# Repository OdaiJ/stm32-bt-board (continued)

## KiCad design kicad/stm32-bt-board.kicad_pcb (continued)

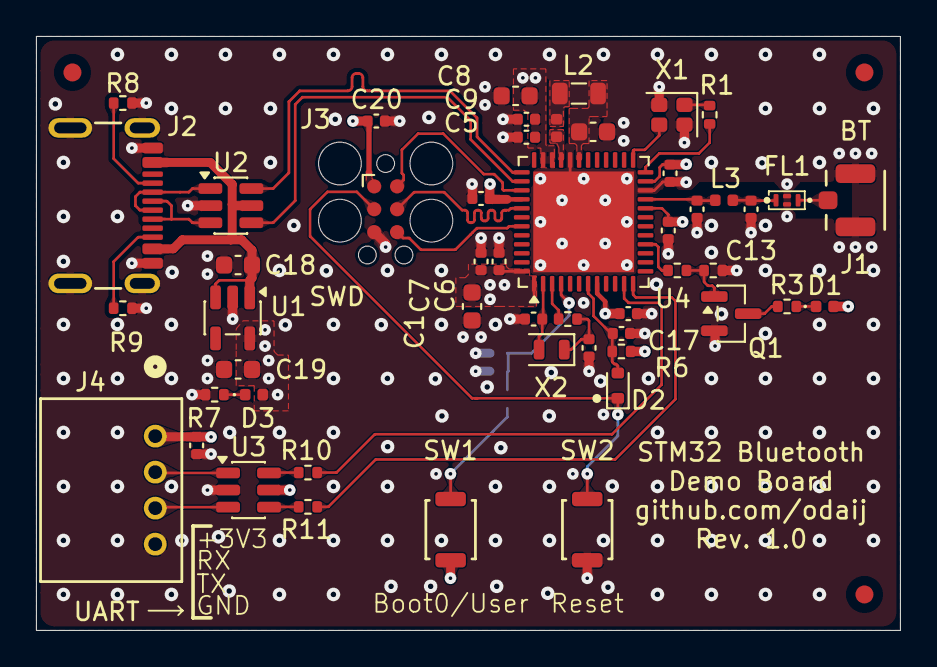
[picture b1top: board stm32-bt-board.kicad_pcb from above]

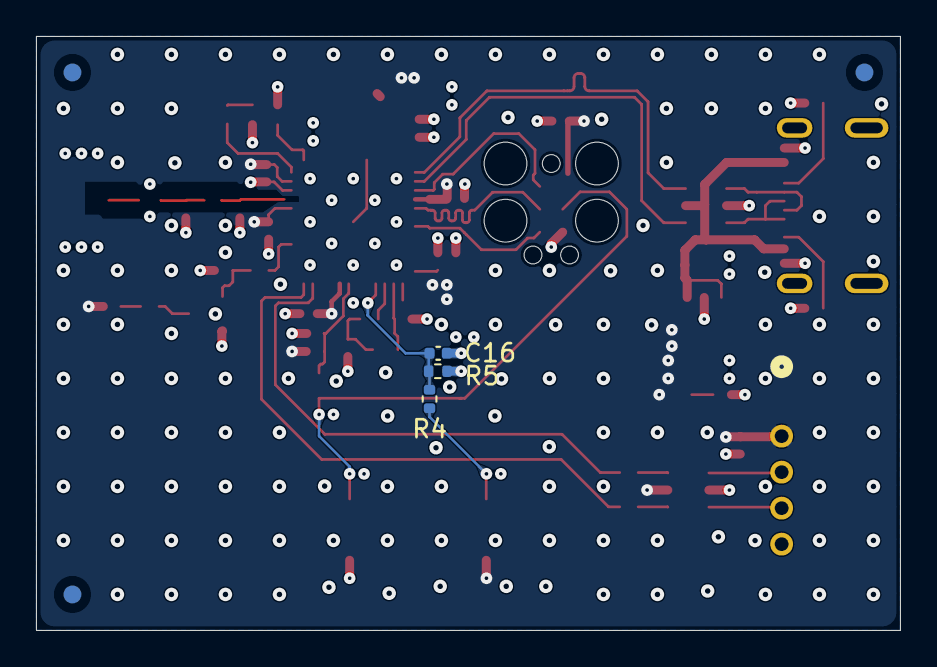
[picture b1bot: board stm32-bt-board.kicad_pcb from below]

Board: 4 copper layers, 48.0 x 33.0 mm, 60 parts (6 on the bottom side), 39 nets.

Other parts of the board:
FID1, FID2, FID3: Fiducial_1mm_Mask2mm
FID4, FID5, FID6: Fiducial; Fiducial_1mm_Mask2mm

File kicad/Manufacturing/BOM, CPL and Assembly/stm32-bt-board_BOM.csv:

"Reference","Qty","Value","DNP","Exclude from BOM","Exclude from Board","Footprint","Datasheet","Distributor","Distributor Link","Manufacturer","MPN","Description"
"C1,C8,C11,C18,C19","5","4u7","","","","Capacitor_SMD:C_0603_1608Metric","https://www.lcsc.com/datasheet/C307467.pdf?spm=wm.sxq.inf.gg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","LCSC","https://www.lcsc.com/product-detail/C307467.html?spm=wm.fly.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","Samsung Electro-Mechanics","CL10A475KL8NRNC","CAP CER 4.7uF 35V X5R 0603"
"C2,C3,C4,C5,C6,C7,C9,C10,C16,C17,C20,C21","12","100n","","","","Capacitor_SMD:C_0402_1005Metric","https://www.lcsc.com/datasheet/C60474.pdf?spm=wm.sxq.inf.ggs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","LCSC","https://www.lcsc.com/product-detail/C60474.html?s_z=s_p_CC04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","YAGEO","CC0402KRX7R7BB104","CAP CER 100nF 16V X7R 0402"
"C12","1","0p8","","","","Capacitor_SMD:C_0402_1005Metric","https://www.lcsc.com/datasheet/C76988.pdf?spm=wm.sxq.inf.ggs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","LCSC","https://www.lcsc.com/product-detail/C76988.html?s_z=s_p_GRM1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","muRata","GRM1555C1HR80BA01D","CAP CER 0.8pF 50V C0G 0402"
"C13","1","0p3","","","","Capacitor_SMD:C_0402_1005Metric","https://www.lcsc.com/datasheet/C92338.pdf?spm=wm.sxq.inf.ggs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","LCSC","https://www.lcsc.com/product-detail/C92338.html?s_z=s_p_GRM1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","muRata","GRM1555C1HR30WA01D","CAP CER 0.3pF 50V C0G 0402"
"C14,C15","2","10p","","","","Capacitor_SMD:C_0402_1005Metric","https://www.lcsc.com/datasheet/C161520.pdf","LCSC","https://www.lcsc.com/product-detail/C161520.html","muRata","GRM1555C1H100FA01D","CAP CER 10pF 50V C0G 0402"
"D1","1","VLMB1500-GS08","","","","LED_SMD:LED_0402_1005Metric","https://www.lcsc.com/datasheet/C511042.pdf?spm=wm.sxq.inf.gg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","LCSC","https://www.lcsc.com/product-detail/C511042.html?s_z=s_p_VLM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","VISHAY","VLMB1500-GS08","LED BLUE 0402 SMD"
"D2","1","BAT54K","","","","Diode_SMD:D_SOD-523","https://www.lcsc.com/datasheet/C283259.pdf?spm=wm.sxq.inf.gg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","LCSC","https://www.lcsc.com/product-detail/C283259.html?s_z=s_p_BAT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","ST","BAT54KFILM","DIODE SCHOTTKY 40V SOD-523"
"D3","1","VLMS1500-GS08","","","","LED_SMD:LED_0402_1005Metric","https://www.lcsc.com/datasheet/C511370.pdf?spm=wm.sxq.inf.gg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","LCSC","https://www.lcsc.com/product-detail/C511370.html?spm=wm.fly.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","VISHAY","VLMS1500-GS08","LED RED 0402 SMD"
"FL1","1","DLF162500LT-5028A1","","","","#stm32-bt-board-external-footprints:DLF162500LT-5028A1","https://product.tdk.com/en/system/files/dam/doc/product/rf/r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","LCSC","https://www.lcsc.com/product-detail/C531364.html?s_z=s_p_DLF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","TDK","DLF162500LT-5028A1","Multilayer Low Pass Filter For 2400-2500MHz"
"J1","1","1909763-1","","","","#stm32-bt-board-external-footprints:1909763-1","https://www.lcsc.com/datasheet/C392444.pdf?spm=wm.sxq.inf.gg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","LCSC","https://www.lcsc.com/product-detail/C392444.html?s_z=s_p_1909763-1","TE Connectivity","1909763-1","CONN RCPT IPEX 50Ω SMD"
"J2","1","2171790001","","","","#stm32-bt-board-external-footprints:2171790001","https://www.molex.com/content/dam/molex/molex-dot-com/produc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","LCSC","https://www.lcsc.com/product-detail/C3197684.html?s_z=s_p_x_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","MOLEX","2171790001","TYPE C 16 PIN TOP MOUNT SMT"
"J4","1","S4B-PH-K-S(LF)(SN)","","","","#stm32-bt-board-external-footprints:S4B-PH-K-S(LF)(SN)","https://www.lcsc.com/datasheet/C157926.pdf?spm=wm.sxq.inf.gg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","LCSC","https://www.lcsc.com/product-detail/C157926.html?s_z=s_p_S4B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","JST","S4B-PH-K-S(LF)(SN)","CONN HEADER TH R/A 4POS 2mm"
"L1","1","10n","","","","Inductor_SMD:L_0402_1005Metric","https://www.lcsc.com/datasheet/C3911026.pdf","LCSC","https://www.lcsc.com/product-detail/C3911026.html?s_z=s_p_LQ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","muRata","LQG15WZ10NJ02D","FIXED IND 10nH 500mA 190mΩ 0402"
"L2","1","10u","","","","Inductor_SMD:L_0805_2012Metric","https://www.lcsc.com/datasheet/C162582.pdf","LCSC","https://www.lcsc.com/product-detail/C162582.html?s_z=n_q_LQM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","muRata","LQM21FN100M80L","FIXED IND 10uH 100mA 390mΩ 0805"
"L3","1","2n7","","","","Inductor_SMD:L_0402_1005Metric","https://www.lcsc.com/datasheet/C77108.pdf?spm=wm.sxq.inf.ggs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","LCSC","https://www.lcsc.com/product-detail/C77108.html?s_z=s_p_LQG1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","muRata","LQG15HS2N7S02D","FIXED IND 2.7nH 800mA 120mΩ 0402"
"Q1","1","S9013-E","","","","Package_TO_SOT_SMD:SOT-23","https://www.lcsc.com/datasheet/C41371419.pdf?spm=wm.sxq.inf.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","LCSC","https://www.lcsc.com/product-detail/C41371419.html?s_z=h_q_S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","MDD(Microdiode Semiconductor)","S9013-E","TRANS NPN 25V 0.5A SOT-23"
"R1,R2,R3","3","0R","","","","Resistor_SMD:R_0402_1005Metric","https://www.lcsc.com/datasheet/C190119.pdf","LCSC","https://www.lcsc.com/product-detail/C190119.html","VISHAY","CRCW04020000Z0ED","RES 0Ω 62.5mW 0402"
"R4,R7,R10,R11","4","220R","","","","Resistor_SMD:R_0402_1005Metric","https://www.lcsc.com/datasheet/C2909336.pdf","LCSC","https://www.lcsc.com/product-detail/C2909336.html","FOJAN","FRC0402F2200TS","RES 220Ω ±1% 62.5mW 0402"
"R5,R8,R9,R13,R16","5","5k1","","","","Resistor_SMD:R_0402_1005Metric","https://www.lcsc.com/datasheet/C105872.pdf","LCSC","https://www.lcsc.com/product-detail/C105872.html","YAGEO","RC0402FR-075K1L","RES 5.1kΩ ±1% 62.5mW 0402"
"R6","1","100k","","","","Resistor_SMD:R_0402_1005Metric","https://www.lcsc.com/datasheet/C60491.pdf","LCSC","https://www.lcsc.com/product-detail/C60491.html","YAGEO","RC0402FR-07100KL","RES 100kΩ ±1% 62.5mW 0402"
"SW1,SW2","2","B3U-1000P","","","","#stm32-bt-board-external-footprints:B3U-1000P","https://www.lcsc.com/datasheet/C231329.pdf?spm=wm.sxq.inf.gg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","LCSC","https://www.lcsc.com/product-detail/C231329.html?s_z=n_q_b3u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","OMRON","B3U-1000P","SWITCH TACTILE SPST 153gf SMD"
"U1","1","MIC5365-3.3YD5","","","","Package_TO_SOT_SMD:TSOT-23-5","https://ww1.microchip.com/downloads/aemDocuments/documents/A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","LCSC","https://www.lcsc.com/product-detail/C626098.html?s_z=n_q_MIC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","MICROCHIP","MIC5365-3.3YD5-TR","150mA Low-dropout Voltage Regulator, Vout 3.3V, Vin up to 5.5V, TSOT-23-5"
"U2,U3","2","USBLC6-2SC6","","","","Package_TO_SOT_SMD:SOT-23-6","https://www.st.com/resource/en/datasheet/usblc6-2.pdf","LCSC","https://www.lcsc.com/product-detail/C7519.html?s_z=s_p_USBLC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","ST","USBLC6-2SC6","Very low capacitance ESD protection diode, 2 data-line, SOT-23-6"
"U4","1","STM32WB55CEU6","","","","Package_DFN_QFN:QFN-48-1EP_7x7mm_P0.5mm_EP5.6x5.6mm","https://www.st.com/resource/en/datasheet/stm32wb55ce.pdf","LCSC","https://www.lcsc.com/product-detail/C911135.html?s_z=s_p_STM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","ST","STM32WB55CEU6","STMicroelectronics Arm Cortex-M4 MCU, 512KB flash, 256KB RAM, 64 MHz, 1.71-3.6V, 30 GPIO, UFQFPN48"
"X1","1","32MHz","","","","Crystal:Crystal_SMD_2016-4Pin_2.0x1.6mm","https://www.lcsc.com/datasheet/C5441424.pdf?spm=wm.sxq.inf.g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","LCSC","https://www.lcsc.com/product-detail/crystals_ndk-nx2016sa-32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","NDK","NX2016SA-32MHZ-EXS00A-CS06654","CRYSTAL 32MHz 8pF SMD"
"X2","1","32kHz768","","","","Crystal:Crystal_SMD_2012-2Pin_2.0x1.2mm","https://www.lcsc.com/datasheet/C891748.pdf?spm=wm.sxq.inf.gg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","LCSC","https://www.lcsc.com/product-detail/C891748.html?s_z=s_p_NX2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","NDK","NX2012SA-32.768KHZ-STD-MUB-2","CRYSTAL 32.768kHz SMD"

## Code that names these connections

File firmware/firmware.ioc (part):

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Mcu.Name=STM32WB55CEUx
Mcu.Package=UFQFPN48
Mcu.UserName=STM32WB55CEUx
PA11.Mode=Device
PA11.Signal=USB_DM
PA12.Mode=Device
PA12.Signal=USB_DP
PA13.Mode=Trace_Asynchronous_SW
PA13.Signal=SYS_JTMS-SWDIO
PA14.Mode=Trace_Asynchronous_SW
PA14.Signal=SYS_JTCK-SWCLK
PA2.Mode=Asynchronous
PA2.Signal=LPUART1_TX
PA3.Mode=Asynchronous
PA3.Signal=LPUART1_RX
PA7.Signal=S_TIM17_CH1
PB3.Mode=Trace_Asynchronous_SW
PB3.Signal=SYS_JTDO-SWO
PC14-OSC32_IN.Mode=LSE-External-Oscillator
PC14-OSC32_IN.Signal=RCC_OSC32_IN
PC15-OSC32_OUT.Mode=LSE-External-Oscillator
PC15-OSC32_OUT.Signal=RCC_OSC32_OUT
RCC.HSE_VALUE=32000000
RCC.SYSCLKFreq_VALUE=64000000
RCC.SYSCLKSource=RCC_SYSCLKSOURCE_PLLCLK
board=custom

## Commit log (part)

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2026-05-15 chore: init
2026-05-15 chore: add a forgotten .gitkeep file to /firmware/
2026-05-16 feat(schematic): add hierarchical sheets, add STM32WB55CEUx power circuitry, and oscillator circuitry, and design notes
    add STM32WB55CEUx symbol and rename package variant suffix from X to 6 to explicitly target the "Industrial temperature range, -40 to 85 °C (105 °C junction)"
    add recommended MCU power decoupling network with a few tweaks following phil's video:
    - 100nF capacitor per VDD-related supply pin placed locally
    - 4.7uF bulk capacitors for VDD and VDDSMPS near the package
    add buck converter topology for the integrated SMPS, suitable for the 4MHz switching frequency, for best power performance
    add HSE and LSE crystal oscillator circuits (incomplete)
2026-05-22 feat(schematic): add RF, SWD, and core MCU support circuitry
    add unvalued capacitors for LSE crystal
    add TDK_DLF162500LT-5028A1 symbol, footprint, and an unverified 3D model
    add RF circuitry
    add SWD circuitry
    add BOOT0 circuitry
    add NRST circuitry
2026-05-22 feat(firmware): add CubeMX configuration for hardware peripherals
    add hardware initializations for SWD, and crystal oscillators
    remove .gitkeep
2026-05-23 feat (schematic): add basmala to root, create new hierarchical sheet for usb inside root, and more /stm32-bt-board/ add basmala to root schematic - add a new usb hierarchical sheet to root
    /stm32-bt-board/Microcontroller/
    - add resistance value for BOOT0 LPF
    /stm32-bt-board/USB/
    - add usb type c receptacle
    - add the usblc6-2sc6 protection ic to D- and D+
    - add 5k1 pull down resistors for CC1 and CC2
2026-05-23 feat (firmware): add USB FS
2026-05-27 A LOT OF STUFF
    I almost finished the schematic part of the tutorial
    what remains is part choosing and filling the relevant fields for every component
2026-06-30 refactor(schematic): polish the schematic as much as possible - add new Basmala - fix netlist names almost EVERYWHERE, this is to help with net classes, and to help with building a good habit of nami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
